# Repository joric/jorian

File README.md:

# Jorian

44-key 16-column wireless split keyboard in a 100x100 mm PCB

## Disclaimer

The keyboard layout is derived from [Jian layout](http://www.keyboard-layout-editor.com/#/gists/4b6c2af67148f58ddd6c6b2976c4370f) (just visually, there was no actual copying involved).
There are multiple [issues](https://github.com/joric/jorian/wiki/Issues) in my version.
Please buy Jian from its author, [/u/KgOfHedgehogs](http://reddit.com/u/KgOfHedgehogs), he's running a high quality commercial batch.

## Download

You can download Gerber files and schematic in the [releases section](https://github.com/joric/jorian/releases).

## Instructions

Please refer to the public [Jorian wiki](https://github.com/joric/jorian/wiki).

## Pictures

### Version 1.0

## References

* Reddit thread: https://www.reddit.com/r/MechanicalKeyboards/comments/aj0mos/jorian_christmas_edition
* My nRF5x QMK fork: https://github.com/joric/qmk_firmware/commits/nrf52

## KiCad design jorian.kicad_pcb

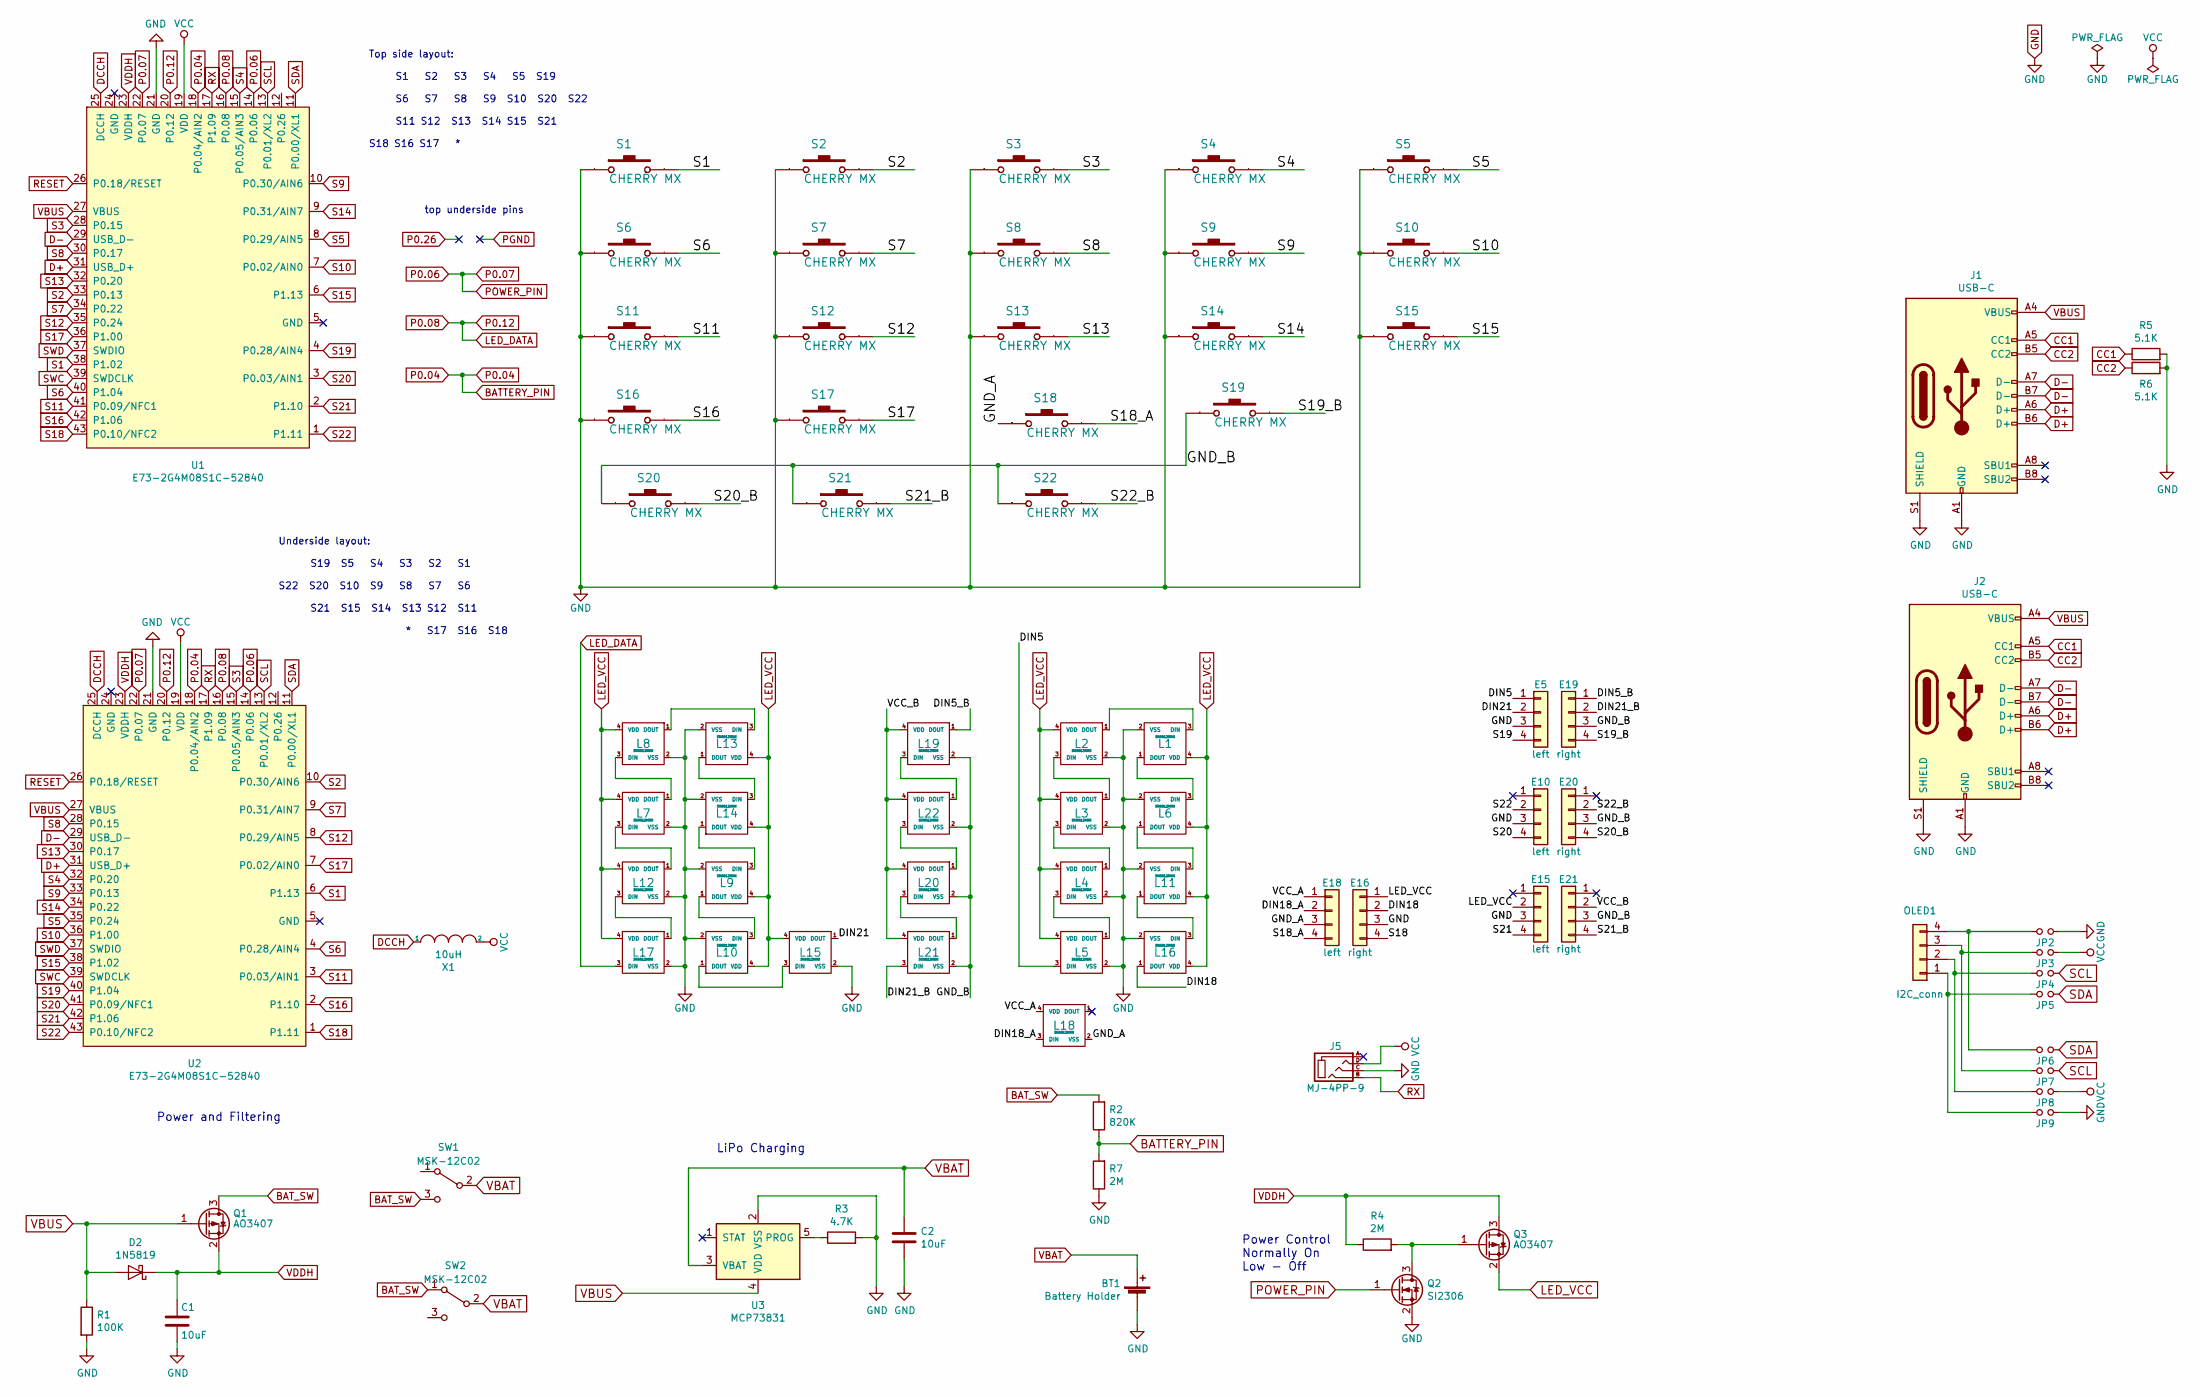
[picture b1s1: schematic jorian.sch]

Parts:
BT1: Battery Holder; cr2032_bs-7
C1, C2: 10uF; C_0603_1608Metric
D2: 1N5819; D_SOD-123
E5, E10, E15, E18: left; edge_conn
E16, E19, E20, E21: right; edge_conn
J1, J2: USB-C; usb_type_c
J5: MJ-4PP-9; trrs_connector
JP2, JP3, JP4, JP5, JP6, JP7, JP8, JP9: jumper
L1, L2, L3, L4, L5, L6, L7, L8, L9, L10, L11, L12, L13, L14, L15, L16, L17, L18, L19, L20, L21, L22: SK6812MINI; kbd_SK6812MINI
OLED1: I2C_conn; connector_swd
Q1, Q3: AO3407; SOT-23
Q2: SI2306; SOT-23
R1: 100K; R_0603_1608Metric
R2: 820K; R_0603_1608Metric
R3: 4.7K; R_0603_1608Metric
R4, R7: 2M; R_0603_1608Metric
R5, R6: 5.1K; R_0603_1608Metric
S1, S2, S3, S4, S5, S6, S7, S8, S9, S10, S11, S12, S13, S14, S15, S16, S17, S18, S19, S20, S21, S22: CHERRY MX; cherry
SW1, SW2: MSK-12C02; switch_MSK-12C02_smd
U1, U2: E73-2G4M08S1C-52840
U3: MCP73831; SOT-23-5
X1: 10uH; L_0603_1608Metric

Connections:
/DIN5: E5.1, L5.3 (DIN)
/DIN5_B: E19.1, L19.1 (DOUT)
/DIN18: E16.2, L16.1 (DOUT)
/DIN18_A: E18.2, L18.3 (DIN)
/DIN21: E5.2, L15.1 (DOUT)
/DIN21_B: E19.2, L21.3 (DIN)
/GND_A: E18.3, L18.2 (VSS), S18.1
/GND_B: E19.3, E20.3, E21.3, L19.2 (VSS), L20.2 (VSS), L21.2 (VSS), L22.2 (VSS), S19.1, S20.1, S21.1, S22.1
/S18_A: E18.4, S18.2
/S19_B: E19.4, S19.2
/S20_B: E20.4, S20.2
/S21_B: E21.4, S21.2
/S22_B: E20.2, S22.2
/VCC_A: E18.1, L18.4 (VDD)
/VCC_B: E21.2, L19.4 (VDD), L20.4 (VDD), L21.4 (VDD), L22.4 (VDD)
BATTERY_PIN: R2.1, R7.2, U1.18 (P0.04/AIN2), U2.18 (P0.04/AIN2)
BAT_SW: Q1.3 (D), R2.2, SW1.3 (C), SW2.1 (A)
CC1: J1.A5 (CC1), J2.A5 (CC1), R5.1
CC2: J1.B5 (CC2), J2.B5 (CC2), R6.1
D+: J1.A6 (D+), J1.B6 (D+), J2.A6 (D+), J2.B6 (D+), U1.31 (USB_D+), U2.31 (USB_D+)
D-: J1.A7 (D-), J1.B7 (D-), J2.A7 (D-), J2.B7 (D-), U1.29 (USB_D-), U2.29 (USB_D-)
DCCH: U1.25 (DCCH), U2.25 (DCCH), X1.1
GND: BT1.2 (-), C1.2, C2.2, E5.3, E10.3, E15.3, E16.3, J1.A1 (GND), J1.A12 (GND), J1.B1 (GND), J1.B12 (GND), J1.S1 (SHIELD), J2.A1 (GND), J2.A12 (GND), J2.B1 (GND), J2.B12 (GND), J2.S1 (SHIELD), J5.C, JP2.1, JP9.1, L1.2 (VSS), L2.2 (VSS), L3.2 (VSS), L4.2 (VSS), L5.2 (VSS), L6.2 (VSS), L7.2 (VSS), L8.2 (VSS), L9.2 (VSS), L10.2 (VSS), L11.2 (VSS), L12.2 (VSS), L13.2 (VSS), L14.2 (VSS), L15.2 (VSS), L16.2 (VSS), L17.2 (VSS), Q2.2 (S), R1.2, R3.2, R5.2, R6.2, R7.1, S1.1, S2.1, S3.1, S4.1, S5.1, S6.1, S7.1, S8.1, S9.1, S10.1, S11.1, S12.1, S13.1, S14.1, S15.1, S16.1, S17.1, U1.21 (GND), U2.21 (GND), U3.2 (VSS)
LED_DATA: L17.3 (DIN), U1.16 (P0.08), U1.20 (P0.12), U2.16 (P0.08), U2.20 (P0.12)
LED_VCC: E15.2, E16.1, L1.4 (VDD), L2.4 (VDD), L3.4 (VDD), L4.4 (VDD), L5.4 (VDD), L6.4 (VDD), L7.4 (VDD), L8.4 (VDD), L9.4 (VDD), L10.4 (VDD), L11.4 (VDD), L12.4 (VDD), L13.4 (VDD), L14.4 (VDD), L15.4 (VDD), L16.4 (VDD), L17.4 (VDD), Q3.2 (S)
unnamed: JP2.2, JP6.2, OLED1.4
unnamed: JP3.2, JP7.2, OLED1.3
unnamed: JP4.2, JP8.2, OLED1.2
unnamed: JP5.2, JP9.2, OLED1.1
unnamed: L1.1 (DOUT), L6.3 (DIN)
unnamed: L1.3 (DIN), L2.1 (DOUT)
unnamed: L2.3 (DIN), L3.1 (DOUT)
unnamed: L3.3 (DIN), L4.1 (DOUT)
unnamed: L4.3 (DIN), L5.1 (DOUT)
unnamed: L7.1 (DOUT), L8.3 (DIN)
unnamed: L10.1 (DOUT), L15.3 (DIN)
unnamed: L9.1 (DOUT), L10.3 (DIN)
unnamed: L11.1 (DOUT), L16.3 (DIN)
unnamed: L6.1 (DOUT), L11.3 (DIN)
unnamed: L7.3 (DIN), L12.1 (DOUT)
unnamed: L12.3 (DIN), L17.1 (DOUT)
unnamed: L13.1 (DOUT), L14.3 (DIN)
unnamed: L8.1 (DOUT), L13.3 (DIN)
unnamed: L9.3 (DIN), L14.1 (DOUT)
unnamed: L19.3 (DIN), L22.1 (DOUT)
unnamed: L20.1 (DOUT), L22.3 (DIN)
unnamed: L20.3 (DIN), L21.1 (DOUT)
unnamed: Q2.3 (D), Q3.1 (G), R4.2
unnamed: R3.1, U3.5 (PROG)
P0.06: Q2.1 (G), U1.14 (P0.06), U1.22 (P0.07), U2.14 (P0.06), U2.22 (P0.07)
RESET: U1.26 (P0.18/RESET), U2.26 (P0.18/RESET)
RX: J5.B, U1.17 (P1.09), U2.17 (P1.09)
S1: S1.2, U1.38 (P1.02), U2.6 (P1.13)
S2: S2.2, U1.33 (P0.13), U2.10 (P0.30/AIN6)
S3: S3.2, U1.28 (P0.15), U2.15 (P0.05/AIN3)
S4: S4.2, U1.15 (P0.05/AIN3), U2.32 (P0.20)
S5: S5.2, U1.8 (P0.29/AIN5), U2.35 (P0.24)
S6: S6.2, U1.40 (P1.04), U2.4 (P0.28/AIN4)
S7: S7.2, U1.34 (P0.22), U2.9 (P0.31/AIN7)
S8: S8.2, U1.30 (P0.17), U2.28 (P0.15)
S9: S9.2, U1.10 (P0.30/AIN6), U2.33 (P0.13)
S10: S10.2, U1.7 (P0.02/AIN0), U2.36 (P1.00)
S11: S11.2, U1.41 (P0.09/NFC1), U2.3 (P0.03/AIN1)
S12: S12.2, U1.35 (P0.24), U2.8 (P0.29/AIN5)
S13: S13.2, U1.32 (P0.20), U2.30 (P0.17)
S14: S14.2, U1.9 (P0.31/AIN7), U2.34 (P0.22)
S15: S15.2, U1.6 (P1.13), U2.38 (P1.02)
S16: S16.2, U1.42 (P1.06), U2.2 (P1.10)
S17: S17.2, U1.36 (P1.00), U2.7 (P0.02/AIN0)
S18: E16.4, U1.43 (P0.10/NFC2), U2.1 (P1.11)
S19: E5.4, U1.4 (P0.28/AIN4), U2.40 (P1.04)
S20: E10.4, U1.3 (P0.03/AIN1), U2.41 (P0.09/NFC1)
S21: E15.4, U1.2 (P1.10), U2.42 (P1.06)
S22: E10.2, U1.1 (P1.11), U2.43 (P0.10/NFC2)
SCL: JP4.1, JP7.1, U1.13 (P0.01/XL2), U2.13 (P0.01/XL2)
SDA: JP5.1, JP6.1, U1.11 (P0.00/XL1), U2.11 (P0.00/XL1)
SWC: U1.39 (SWDCLK), U2.39 (SWDCLK)
SWD: U1.37 (SWDIO), U2.37 (SWDIO)
VBAT: BT1.1 (+), C2.1, SW1.2 (B), SW2.2 (B), U3.3 (VBAT)
VBUS: D2.2 (A), J1.A4 (VBUS), J1.A9 (VBUS), J1.B4 (VBUS), J1.B9 (VBUS), J2.A4 (VBUS), J2.A9 (VBUS), J2.B4 (VBUS), J2.B9 (VBUS), Q1.1 (G), R1.1, U1.27 (VBUS), U2.27 (VBUS), U3.4 (VDD)
VCC: J5.D, JP3.1, JP8.1, U1.19 (VDD), U2.19 (VDD), X1.2
VDDH: C1.1, D2.1 (K), Q1.2 (S), Q3.3 (D), R4.1, U1.23 (VDDH), U2.23 (VDDH)

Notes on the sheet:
Power and Filtering
LiPo Charging
top underside pins
Power Control Normally On Low - Off
Top side layout: S1 S2 S3 S4 S5 S19 S6 S7 S8 S9 S10 S20 S22 S11 S12 S13 S14 S15 S21 S18 S16 S17 *
Underside layout: S19 S5 S4 S3 S2 S1 S22 S20 S10 S9 S8 S7 S6 S21 S15 S14 S13 S12 S11 * S17 S16 S18

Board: 2 copper layers, 84 parts (22 on the bottom side), 82 nets, no tracks yet.

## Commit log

2018-12-18 second commit
2018-12-19 added charger
2018-12-19 autorouted charger take 1
2018-12-20 autorouted charger take 2
2018-12-20 autorouted version with better usb-c
2018-12-21 autorouted charger, alpha version
2018-12-21 autorouted alpha, better placement
2018-12-21 updated placement
2018-12-24 separate charger
2018-12-24 separate charger all
2018-12-24 sent files
2018-12-24 charger with holes, autorouted
2018-12-24 updated layout
2018-12-25 edge cuts 0.2 tolerance 0.175
2018-12-25 reroute take 3, moved a bit by hand
2019-01-09 pushed to version 1.0
2019-01-21 added license
2019-01-23 added picture
2019-03-10 updated video
2019-03-16 updated readme, added precompiled firmware
2019-03-16 updated readme, added link to Jian layout
2019-03-16 updated readme, added layout
2019-03-16 updated picture
2019-04-16 added more PCB issues
2019-08-19 fixed li-po charger jumpers on the back side
2019-09-19 removed files
2019-09-19 Added unlicense
2019-09-19 discontinued, added unlicense, feel free to sell copy and modify
2019-11-24 updated files
2019-12-17 latest changes
2019-12-17 added disclaimer
2020-02-20 autorouted
2020-02-20 better nr52 symbol, autorouted
2020-02-21 fully autorouted (leds are still on internal DCDC, not good)
2020-02-21 LEDs power moved to to VDDH, autorouted
2020-02-21 fixed VBUS, autorouted
2020-02-21 fixed usb footprints, autorouted
2020-02-22 enforced sw1 footprint
2020-03-12 fixed schematic, not routed
2020-05-19 updated pcb
2020-05-24 added reverse mount sk6812mini-e kicad footprint
